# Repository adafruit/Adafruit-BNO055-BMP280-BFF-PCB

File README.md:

## Adafruit BNO055 + BMP280 BFF Add-On for QT Py PCB

<a href="http://www.adafruit.com/products/5937"><br/>
Click here to purchase one from the Adafruit shop</a>

PCB files for the Adafruit BNO055 + BMP280 BFF Add-On for QT Py. 

Format is EagleCAD schematic and board layout
* https://www.adafruit.com/product/5937

### Description

Our QT Py boards are a great way to make very small microcontroller projects that pack a ton of power - and now we have a way for you to turn many QT Py boards into powerful 9 degree-of-freedom (9DoF) motion plus pressure/altitude sensing projects that are super small!

We call this the Adafruit BNO055 + BMP280 BFF—a "Best Friend Forever." When you were a kid, you may have learned about the "buddy" system; well, this product is kind of like that! It's a board that will watch your QT Py's back and give it more capabilities.

This PCB is designed to fit onto the back of any QT Py or Xiao board. It can be soldered into place or made removable using pin and socket headers.

Rather than spending weeks or months fiddling with algorithms of varying accuracy and complexity, you can have meaningful sensor data in minutes thanks to the BNO055. This smart 9-DOF sensor does the sensor fusion all on its own!  You can read the data right over I2C and Bob's yer uncle.

The BNO055 can output the following sensor data:

* Absolute Orientation (Euler Vector, 100Hz) Three axis orientation data based on a 360° sphere
* Absolute Orientation (Quaternion, 100Hz) Four point quaternion output for more accurate data manipulation
* Angular Velocity Vector (100Hz) Three axis of 'rotation speed' in rad/s
* Acceleration Vector (100Hz) Three axis of acceleration (gravity + linear motion) in m/s^2
* Magnetic Field Strength Vector (20Hz) Three axis of magnetic field sensing in micro Tesla (uT)
* Linear Acceleration Vector (100Hz) Three axis of linear acceleration data (acceleration minus gravity) in m/s^2
* Gravity Vector (100Hz) Three axis of gravitational acceleration (minus any movement) in m/s^2
* Temperature (1Hz) Ambient temperature in degrees celsius

The only thing it doesn't have is barometric pressure, which can be used for altitude calculations. Aha, that's why there's also a BMP280 sensor on board. This precision sensor from Bosch is the best low-cost, precision sensing solution for measuring barometric pressure with ±1 hPa absolute accuracy, and temperature with ±1.0°C accuracy. Because pressure changes with altitude and the pressure measurements are so good, you can also use it as an altimeter with  ±1 meter accuracy.

Usage for the BFF is simple is simple, because both the BNO and BMP talk over I2C - so you'll just use the SDA/SCL pins. Note that some QT Py boards with a Stemma QT port have two I2C ports, so make sure you are using the port that's on the SDA/SCL pins, not the QT port! There's optional Interrupt/Reset pins for the BNO055 if you want more advanced control, and each sensor also has address-changing jumpers in case you want to switch from the default addresses of BMP280 @ 0x76 and BNO055 @ 0x38.

If you'd like, you can solder the BFF directly on the back of your Xiao/QT Py or use the included header to solder each side to your QT Py to make a sandwich. You can also pick up an Itsy Bitsy short female header kit to make it removable but compact; you'll need to trim the headers to 7 pins long.

QT Py is not included! 

### License

Adafruit invests time and resources providing this open source design, please support Adafruit and open-source hardware by purchasing products from [Adafruit](https://www.adafruit.com)!

Designed by Limor Fried/Ladyada for Adafruit Industries.

Creative Commons Attribution/Share-Alike, all text above must be included in any redistribution. 
See license.txt for additional details.

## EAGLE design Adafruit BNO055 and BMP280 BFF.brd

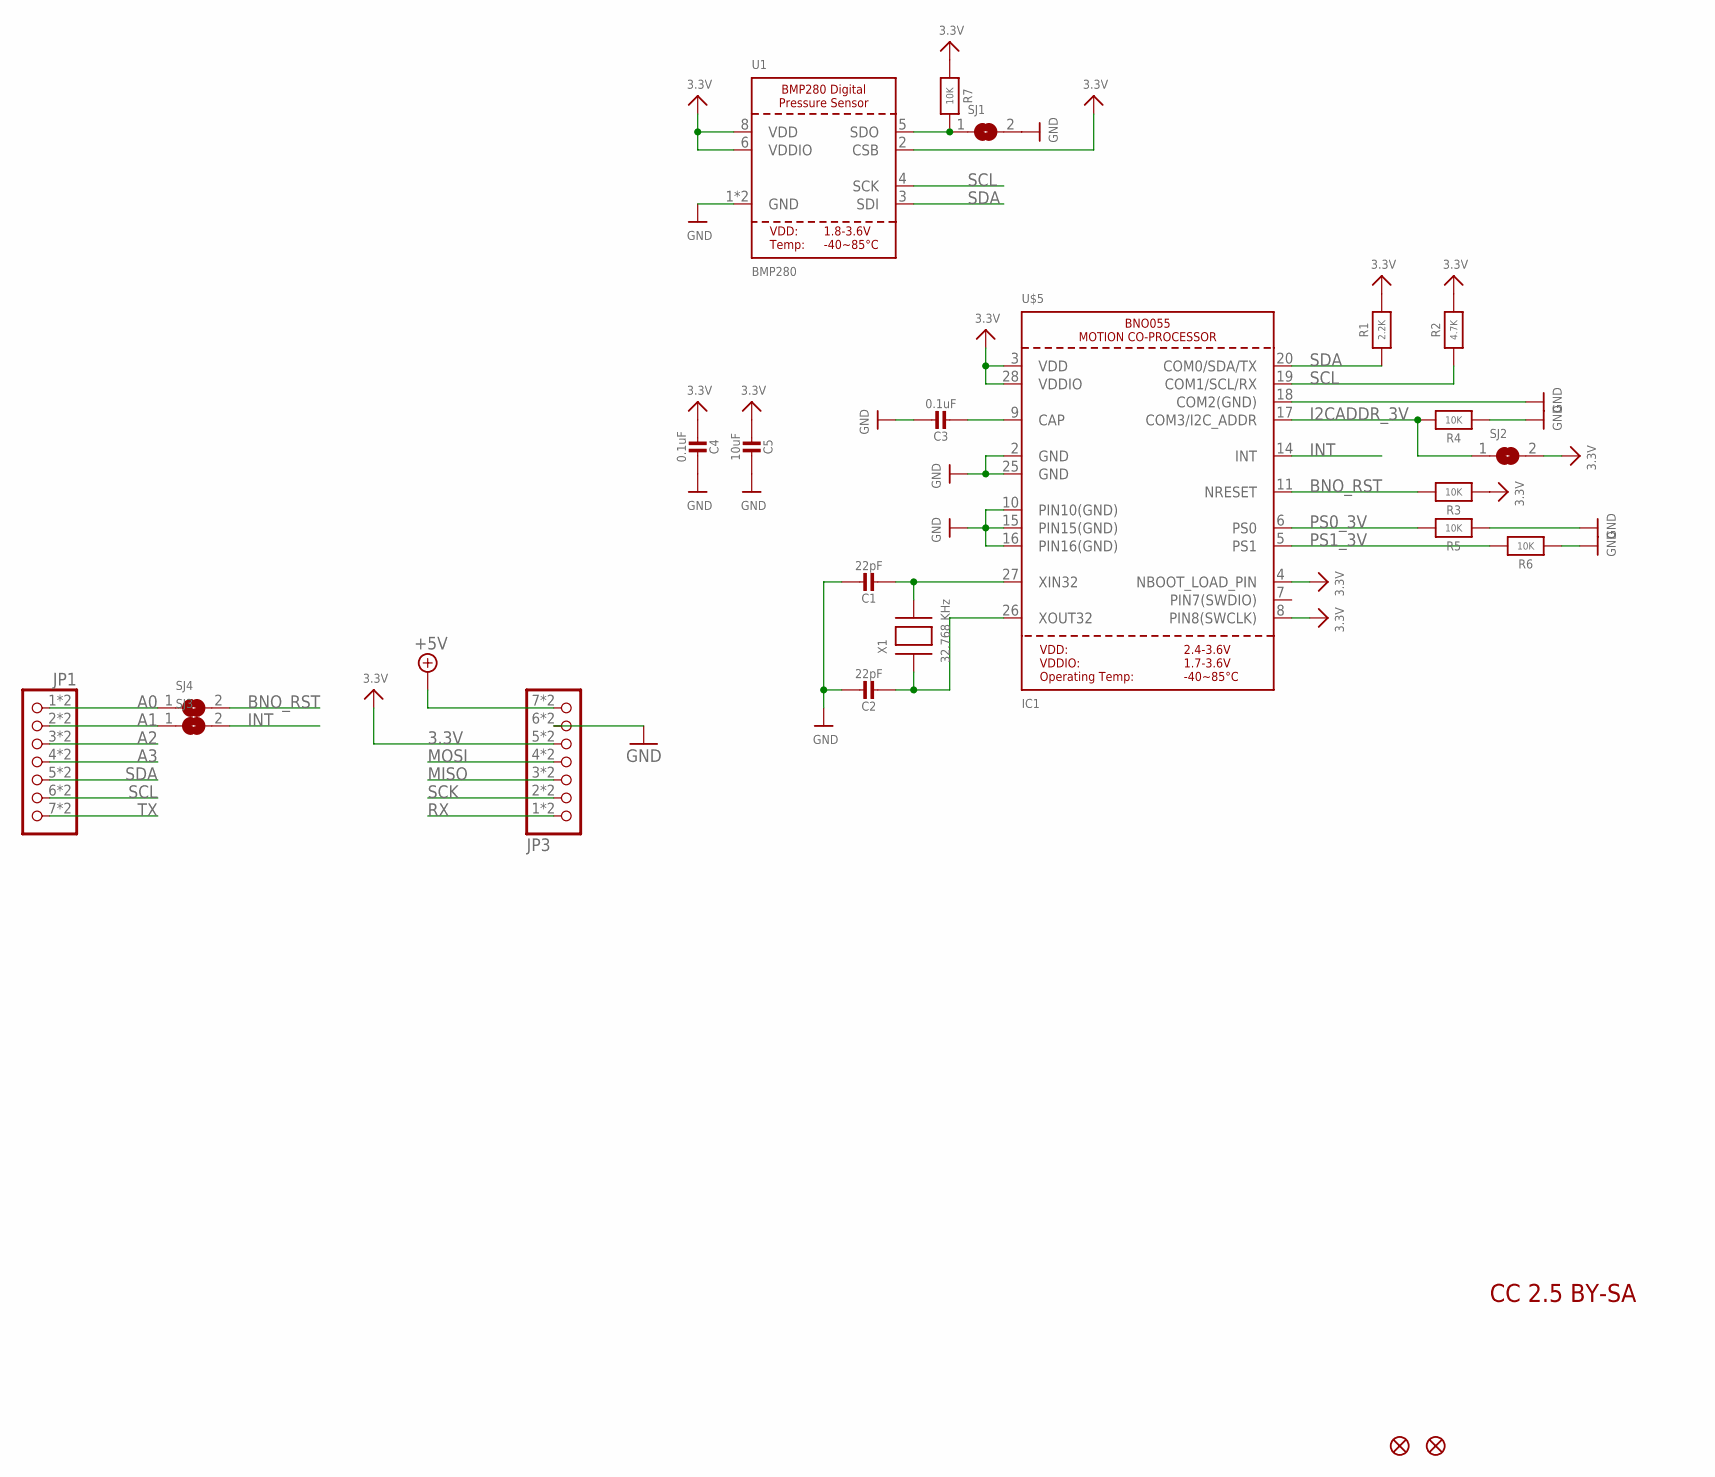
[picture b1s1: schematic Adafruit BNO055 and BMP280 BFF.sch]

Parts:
C1, C2: 22pF; 0603-NO
C3, C4: 0.1uF; 0603-NO
C5: 10uF; 0805-NO
JP1, JP3: HEADER-1X7_CASTEL; 1X07_CASTEL
R1: 2.2K; 0603-NO
R2: 4.7K; 0603-NO
R3, R4, R5, R6, R7: 10K; 0603-NO
SJ1, SJ2, SJ3, SJ4: SOLDERJUMPER; SOLDERJUMPER_ARROW_NOPASTE
U1: BMP280
U$5: IC1; BNO055
U$6, U$8: FIDUCIAL_0.5MM
X1: 32.768 KHz; XTAL3215

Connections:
3.3V: C4.2, C5.2, JP3.5, JP3.5C (5), R1.2, R2.2, R3.1, R7.1, SJ2.2, U1.2 (CSB), U1.6 (VDDIO), U1.8 (VDD), U$5.3 (VDD), U$5.4 (NBOOT_LOAD_PIN), U$5.8 (PIN8(SWCLK)), U$5.28 (VDDIO)
+5V: JP3.7, JP3.7C (7)
A0: JP1.1, JP1.1C (1), SJ4.1
A1: JP1.2, JP1.2C (2), SJ3.1
A2: JP1.3, JP1.3C (3)
A3: JP1.4, JP1.4C (4)
BNO_RST: R3.2, SJ4.2, U$5.11 (NRESET)
GND: C1.1, C2.1, C3.1, C4.1, C5.1, JP3.6, JP3.6C (6), R4.1, R5.1, R6.1, SJ1.2, U1.1 (GND), U1.7 (GND), U$5.2 (GND), U$5.10 (PIN10(GND)), U$5.15 (PIN15(GND)), U$5.16 (PIN16(GND)), U$5.18 (COM2(GND)), U$5.25 (GND)
I2CADDR_3V: R4.2, SJ2.1, U$5.17 (COM3/I2C_ADDR)
INT: SJ3.2, U$5.14 (INT)
MISO: JP3.3, JP3.3C (3)
MOSI: JP3.4, JP3.4C (4)
unnamed: C1.2, U$5.27 (XIN32), X1.P$2
unnamed: C2.2, U$5.26 (XOUT32), X1.P$1
unnamed: C3.2, U$5.9 (CAP)
unnamed: R7.2, SJ1.1, U1.5 (SDO)
PS0_3V: R5.2, U$5.6 (PS0)
PS1_3V: R6.2, U$5.5 (PS1)
RX: JP3.1, JP3.1C (1)
SCK: JP3.2, JP3.2C (2)
SCL: JP1.6, JP1.6C (6), R2.1, U1.4 (SCK), U$5.19 (COM1/SCL/RX)
SDA: JP1.5, JP1.5C (5), R1.1, U1.3 (SDI), U$5.20 (COM0/SDA/TX)
TX: JP1.7, JP1.7C (7)

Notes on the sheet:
CC 2.5 BY-SA

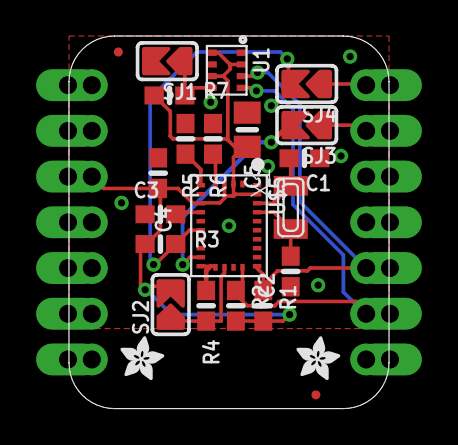
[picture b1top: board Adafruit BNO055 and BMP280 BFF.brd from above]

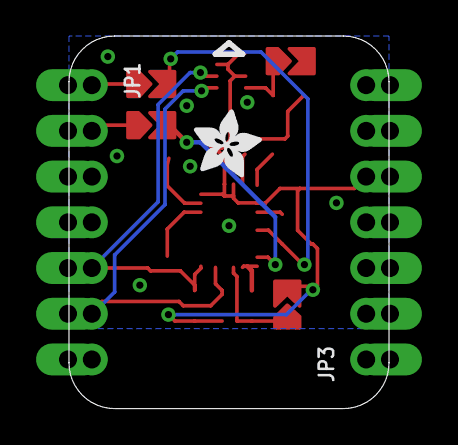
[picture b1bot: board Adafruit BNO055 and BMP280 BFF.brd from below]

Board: 2 copper layers, 17.8 x 20.7 mm, 44 parts (6 on the bottom side), 23 nets.

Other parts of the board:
PLABEL0: PLABEL0
PLABEL1: PLABEL1
PLABEL2: PLABEL2
PLABEL3: PLABEL3
PLABEL4: PLABEL4
PLABEL5: PLABEL5
PLABEL6: PLABEL6
PLABEL7: PLABEL7
PLABEL8: PLABEL8
PLABEL9: PLABEL9
PLABEL10: PLABEL10
PLABEL11: PLABEL11
PLABEL12: PLABEL12
PLABEL13: PLABEL13
PLABEL14: PLABEL14
PLABEL15: PLABEL15
PLABEL16: PLABEL16
PLABEL17: PLABEL17
U$2: ADAFRUIT_3.5MM
U$30, U$31: ADAFRUIT_2.5MM

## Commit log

2024-04-16 cookiecutter

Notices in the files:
parts and their libraries:
microbuilder: This work is placed in the public domain, and may be freely used for commercial and non-commercial work with the following conditions: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
